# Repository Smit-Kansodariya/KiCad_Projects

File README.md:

# KiCad Projects - My PCB Designs 
## Overview
This repository contains the **KiCad design files**.  
It includes the **schematic diagram**, **PCB layout**, and a **3D model view** of the final custom board.

The goal of this project is to design a custom PCB using KiCad.

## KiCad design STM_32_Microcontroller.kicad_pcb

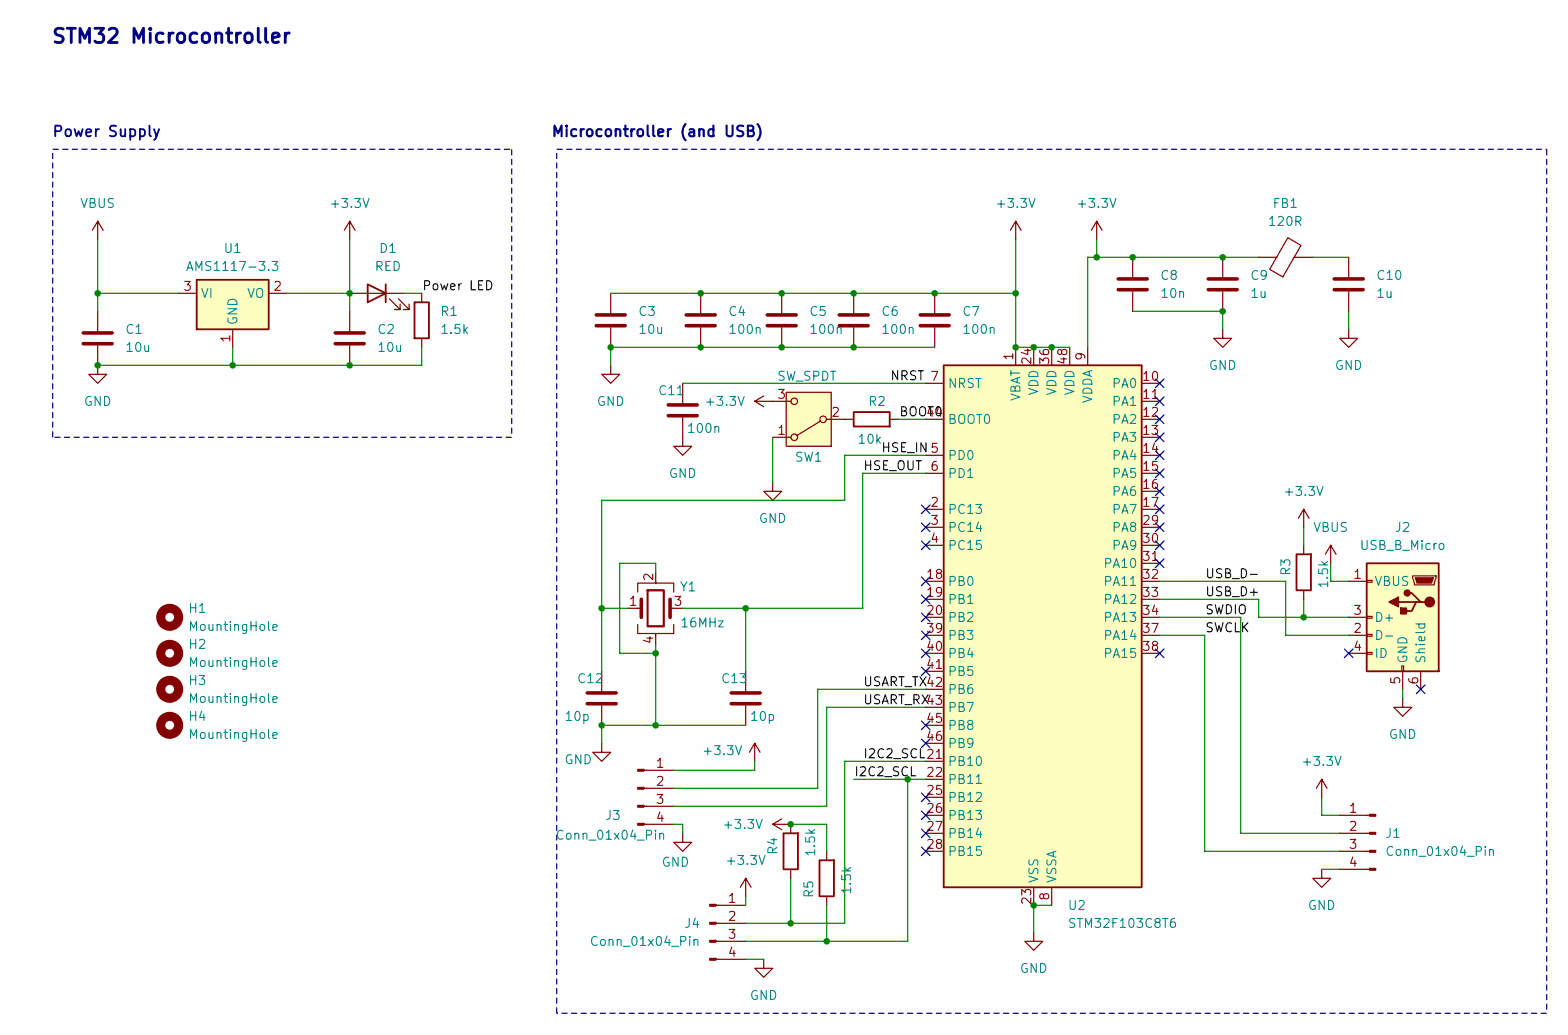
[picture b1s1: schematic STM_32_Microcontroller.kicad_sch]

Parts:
C1, C2, C3: 10u; C_0603_1608Metric
C4, C5, C6, C7, C11: 100n; C_0402_1005Metric
C8: 10n; C_0402_1005Metric
C9, C10: 1u; C_0402_1005Metric
C12, C13: 10p; C_0402_1005Metric
D1: RED; LED_0603_1608Metric
FB1: 120R; L_0603_1608Metric
H1, H2, H3, H4: MountingHole; MountingHole_2.1mm
J1, J3, J4: Conn_01x04_Pin; PinHeader_1x04_P2.54mm_Vertical
J2: USB_B_Micro; USB_Micro-B_Wuerth_629105150521
R1, R3, R4, R5: 1.5k; R_0402_1005Metric
R2: 10k; R_0402_1005Metric
SW1: SW_SPDT; SW_E-Switch_EG1224_SPDT_Angled
U1: AMS1117-3.3; SOT-223-3_TabPin2
U2: STM32F103C8T6; LQFP-48_7x7mm_P0.5mm
Y1: 16MHz; Crystal_SMD_3225-4Pin_3.2x2.5mm

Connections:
+3.3V: C2.1, C3.1, C4.1, C5.1, C6.1, C7.1, C8.1, C9.1, D1.2 (A), FB1.1, J1.1, J3.1, J4.1, R3.2, R4.2, R5.2, SW1.3 (C), U1.2 (VO), U2.1 (VBAT), U2.9 (VDDA), U2.24 (VDD), U2.36 (VDD), U2.48 (VDD)
/BOOT0: R2.2, U2.44 (BOOT0)
/HSE_IN: C12.1, U2.5 (PD0), Y1.1
/HSE_OUT: C13.1, U2.6 (PD1), Y1.3
/I2C2_SCL: J4.2, J4.3, R4.1, R5.1, U2.21 (PB10), U2.22 (PB11)
/NRST: C11.1, U2.7 (NRST)
/Power LED: D1.1 (K), R1.1
/SWCLK: J1.3, U2.37 (PA14)
/SWDIO: J1.2, U2.34 (PA13)
/USART_RX: J3.3, U2.43 (PB7)
/USART_TX: J3.2, U2.42 (PB6)
/USB_D+: J2.3 (D+), R3.1, U2.33 (PA12)
/USB_D-: J2.2 (D-), U2.32 (PA11)
GND: C1.2, C2.2, C3.2, C4.2, C5.2, C6.2, C7.2, C8.2, C9.2, C10.2, C11.2, C12.2, C13.2, J1.4, J2.5 (GND), J3.4, J4.4, R1.2, SW1.1 (A), U1.1 (GND), U2.8 (VSSA), U2.23 (VSS), U2.35 (VSS), U2.47 (VSS), Y1.2, Y1.4
unnamed: C10.1, FB1.2
unnamed: R2.1, SW1.2 (B)
VBUS: C1.1, J2.1 (VBUS), U1.3 (VI)

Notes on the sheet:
STM32 Microcontroller
Power Supply
Microcontroller (and USB)

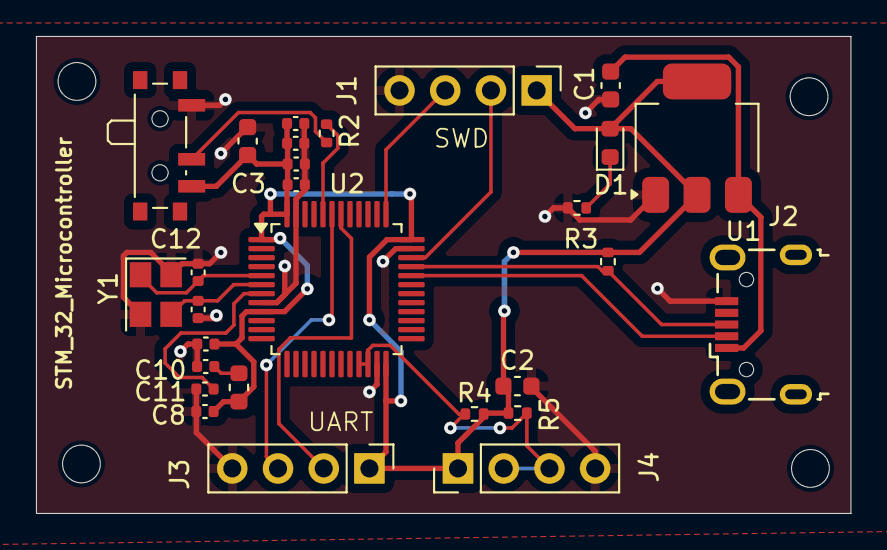
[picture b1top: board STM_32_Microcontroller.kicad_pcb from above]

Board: 2 copper layers, 45.2 x 26.5 mm, 32 parts (0 on the bottom side), 17 nets.

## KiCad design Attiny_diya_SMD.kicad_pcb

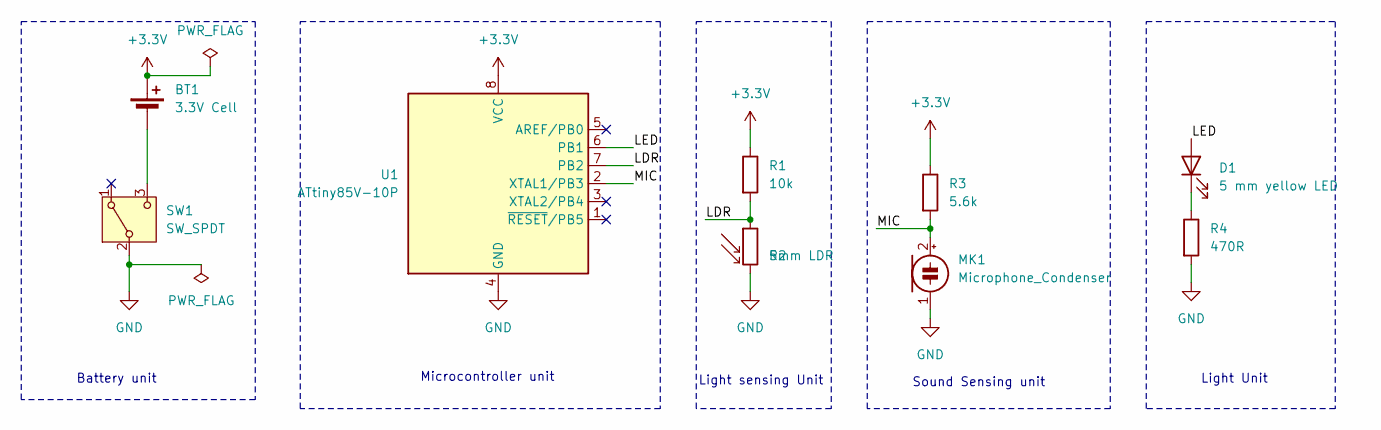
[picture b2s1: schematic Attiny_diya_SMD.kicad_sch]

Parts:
BT1: 3.3V Cell; BatteryHolder_ComfortableElectronic_CH273-2450_1x2450
D1: 5 mm yellow LED; LED_D5.0mm
MK1: Microphone_Condenser; PinHeader_1x02_P2.54mm_Vertical
R1: 10k; R_Axial_DIN0207_L6.3mm_D2.5mm_P15.24mm_Horizontal
R2: 5mm LDR; R_LDR_5.1x4.3mm_P3.4mm_Vertical
R3: 5.6k; R_Axial_DIN0207_L6.3mm_D2.5mm_P15.24mm_Horizontal
R4: 470R; R_Axial_DIN0207_L6.3mm_D2.5mm_P15.24mm_Horizontal
SW1: SW_SPDT; SW_E-Switch_EG1224_SPDT_Angled
U1: ATtiny85V-10P; DIP-8_W7.62mm

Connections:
+3.3V: BT1.1 (+), R1.1, R3.1, U1.8 (VCC)
/LDR: R1.2, R2.1, U1.7 (PB2)
/LED: D1.2 (A), U1.6 (PB1)
/MIC: MK1.2 (+), R3.2, U1.2 (XTAL1/PB3)
GND: MK1.1 (-), R2.2, R4.2, SW1.2 (B), U1.4 (GND)
unnamed: BT1.2 (-), SW1.3 (C)
unnamed: D1.1 (K), R4.1

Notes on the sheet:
Sound Sensing unit
Light Unit
Microcontroller unit
Light sensing Unit
Battery unit

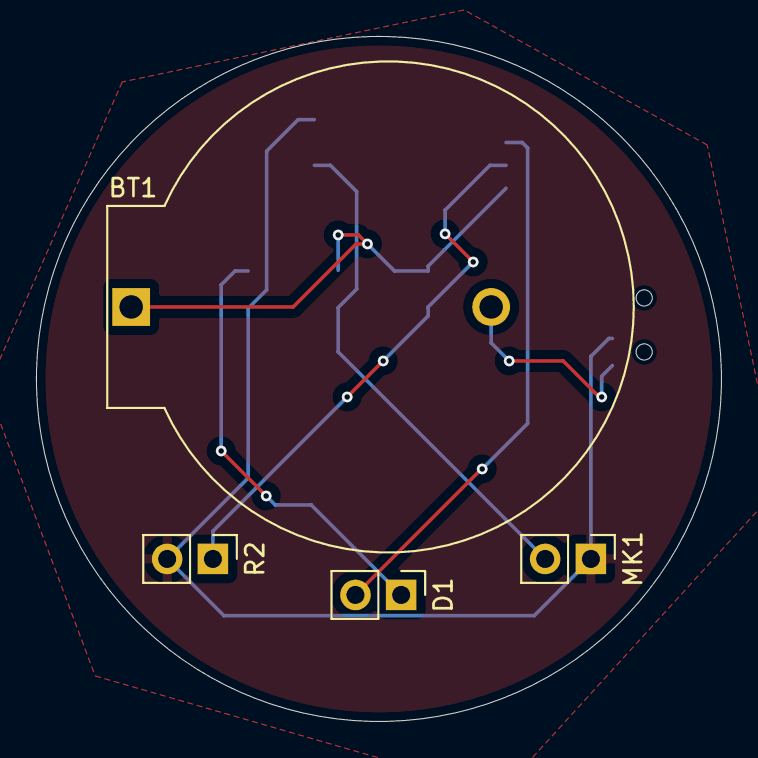
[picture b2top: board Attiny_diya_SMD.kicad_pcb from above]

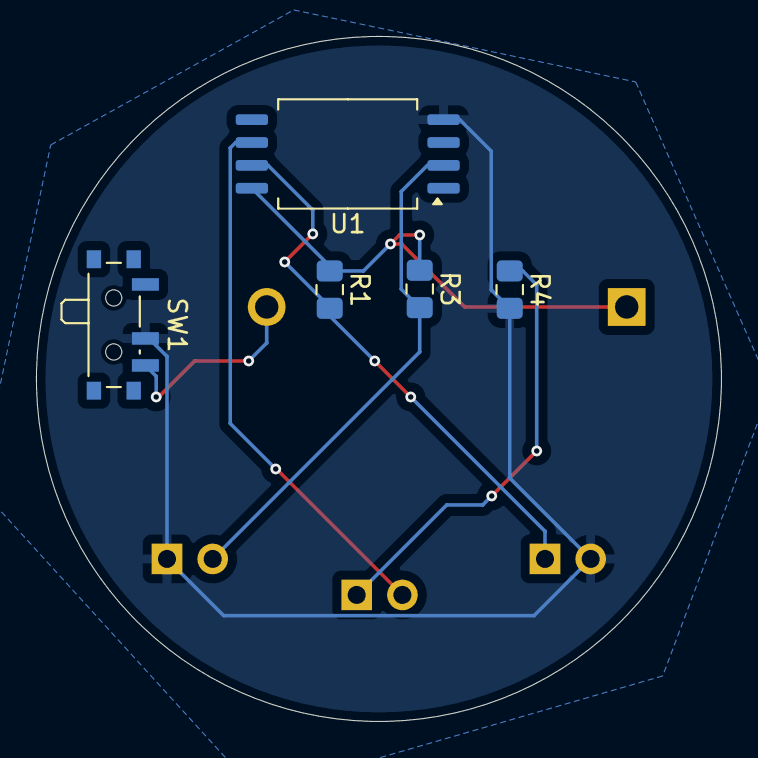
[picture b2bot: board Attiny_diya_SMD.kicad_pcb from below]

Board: 2 copper layers, 38.1 x 38.1 mm, 9 parts (5 on the bottom side), 7 nets.

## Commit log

2024-05-07 This is my PCB designs using KiCad
2025-11-07 Create STM_32_pcb_schematic
2025-11-07 Create Automatic_Diya_Schematic
2025-11-07 Attiny_diya_SMD.kicad_pcb
2025-11-07 Attiny_PCB_schematic
2025-11-07 STM32_PCB_schematic
2025-11-07 README.md
2025-11-07 PCB Layout
